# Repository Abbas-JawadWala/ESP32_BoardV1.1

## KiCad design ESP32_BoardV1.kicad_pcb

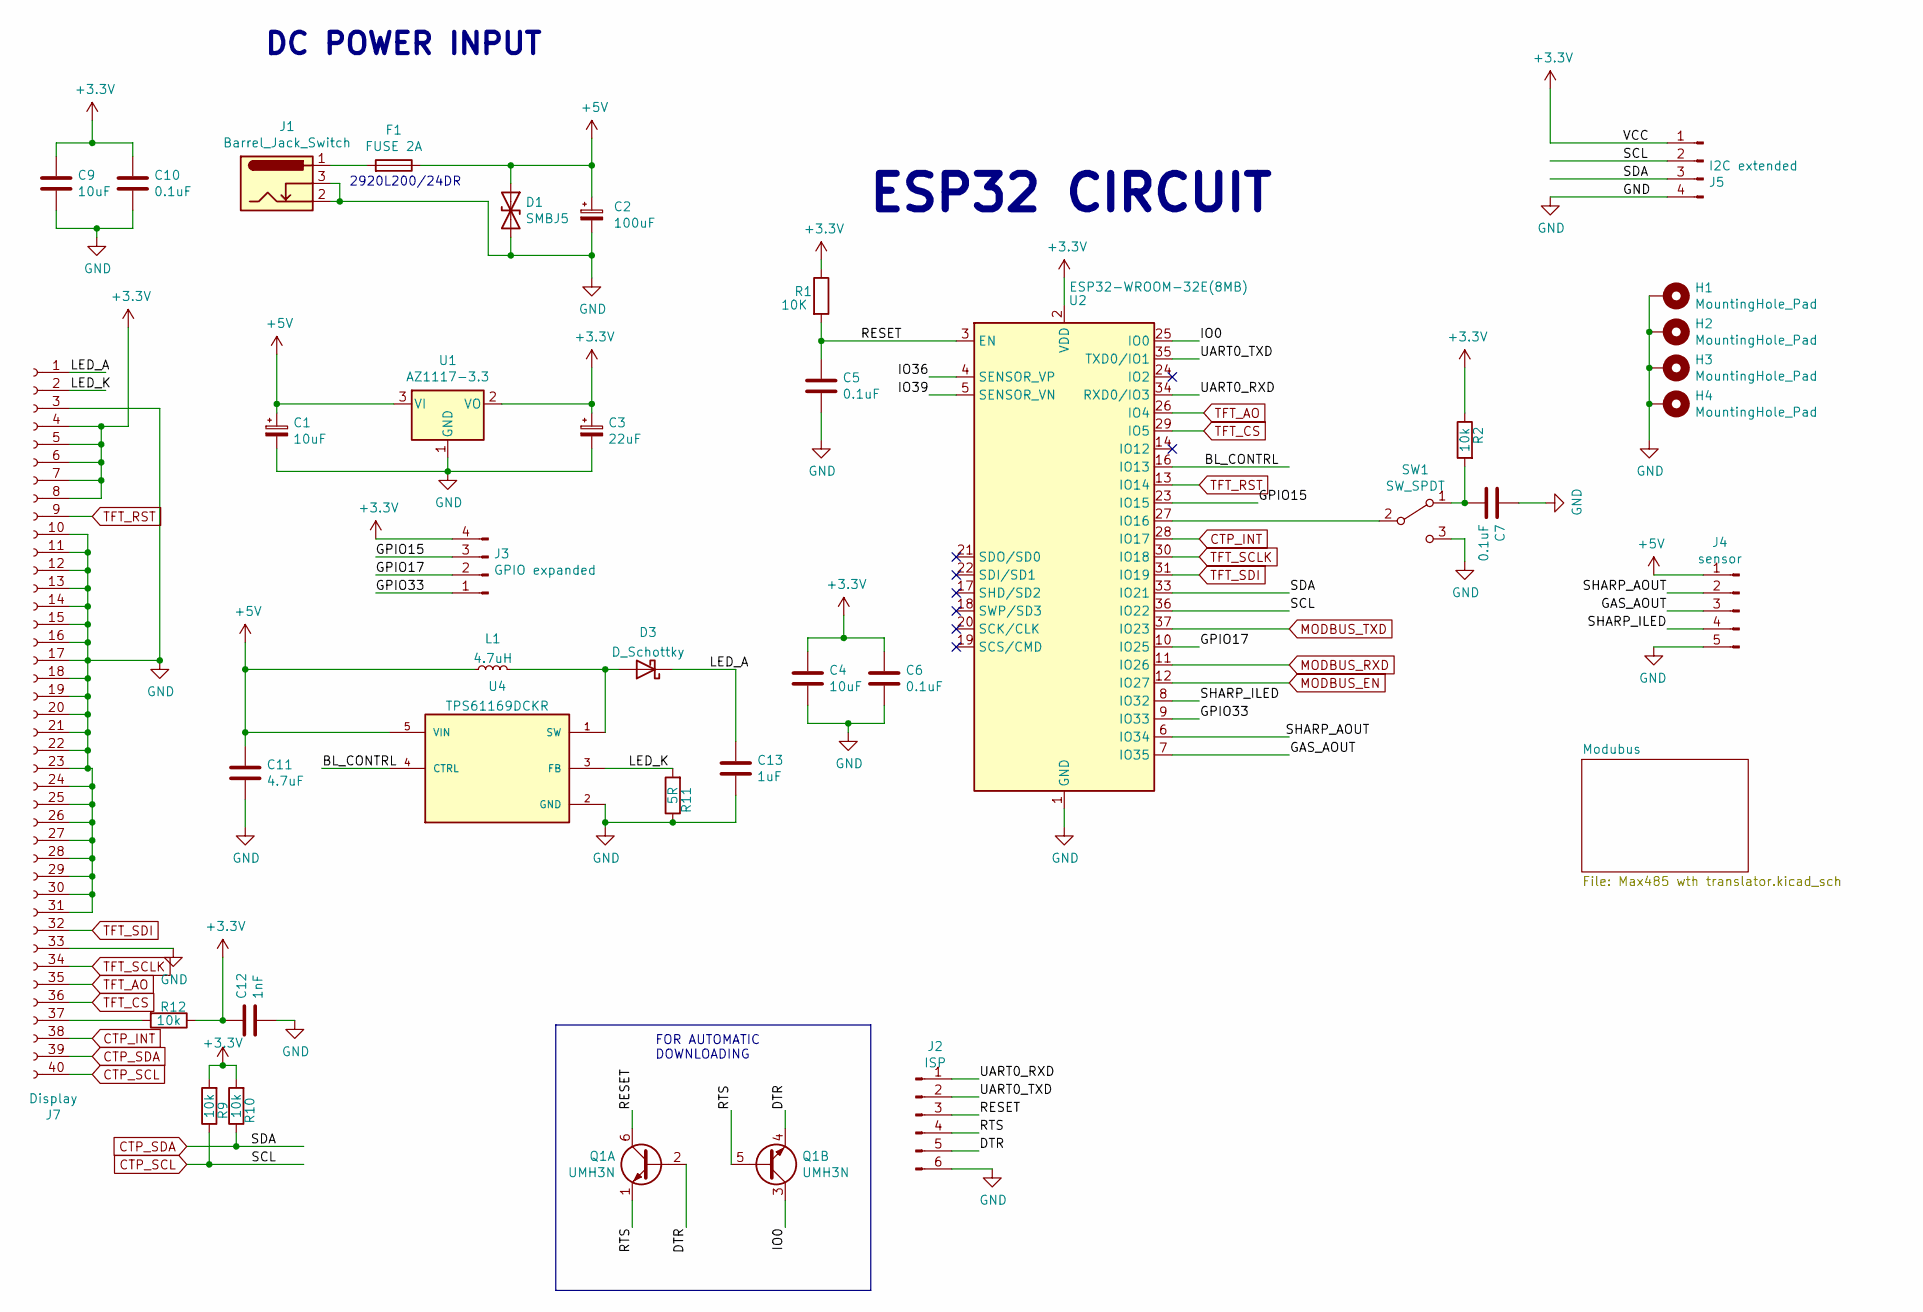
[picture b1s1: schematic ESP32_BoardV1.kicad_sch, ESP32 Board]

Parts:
C1: 10uF; CP_Elec_3x5.4
C2: 100uF; CP_Elec_6.3x5.4
C3: 22uF; CP_Elec_5x5.4
C4, C9: 10uF; C_0402_1005Metric_Pad0.74x0.62mm_HandSolder
C5, C6, C7, C10: 0.1uF; C_0402_1005Metric_Pad0.74x0.62mm_HandSolder
C11: 4.7uF; C_0402_1005Metric; MPN C1005X5R1A475K050BC
C12: 1nF; C_0402_1005Metric; MPN 0402ZC102KAT2A
C13: 1uF; C_0402_1005Metric; MPN C1005X6S1A105K050BC
D1: SMBJ5; D_SMB
D3: D_Schottky; D_SOD-123F; MPN RB160MM-90TR
F1: FUSE 2A; Fuse_1206_3216Metric
H1, H2, H3, H4: MountingHole_Pad; MountingHole_4.3mm_M4_Pad_Via
J1: Barrel_Jack_Switch; BarrelJack_CLIFF_FC681465S_SMT_Horizontal
J2: ISP; PinHeader_1x06_P2.54mm_Vertical
J3: GPIO expanded; JST_SM04B-SRSS-TB(LF)(SN); MPN JST_SM04B-SRSS-TB(LF)(SN)
J4: sensor; JST_SM05B-SRSS-TB(LF)(SN); MPN JST_SM05B-SRSS-TB(LF)(SN)
J5: I2C extended; JST_SM04B-SRSS-TB(LF)(SN); MPN JST_SM04B-SRSS-TB(LF)(SN)
J7: Display; Hirose_FH12-40S-0.5SH_1x40-1MP_P0.50mm_Horizontal
L1: 4.7uH; L_1008_2520Metric; MPN NRS4018T100MDGJ
Q1: UMH3N; SOT-363_SC-70-6
R1: 10K; R_0402_1005Metric_Pad0.72x0.64mm_HandSolder
R2, R9, R10, R12: 10k; R_0402_1005Metric_Pad0.72x0.64mm_HandSolder
R11: 5R; R_0402_1005Metric_Pad0.72x0.64mm_HandSolder
SW1: SW_SPDT; SW_Slide_1P2T_CK_OS102011MS2Q
U1: AZ1117-3.3; SOT-223-3_TabPin2; MPN AZ1117-3.3
U2: ESP32-WROOM-32E(8MB); ESP32-WROOM-32; MPN ESP32-WROOM-32
U4: TPS61169DCKR; SOT-353_SC-70-5; PARTREV A

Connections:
+3V3: C3.1, C4.1, C6.1, C9.1, C10.1, C12.1, J3.4, J5.1, J7.4, J7.5, J7.6, J7.7, J7.8, R1.1, R2.1, R9.2, R10.2, R12.1, U1.2 (VO), U2.2 (VDD); also elsewhere on the board
+5V: C1.1, C2.1, C11.1, D1.1 (A1), F1.1, J4.1, L1.1, U1.3 (VI), U4.5 (VIN)
/BL_CONTRL: U2.16 (IO13), U4.4 (CTRL)
/DTR: J2.5, Q1.2 (B1), Q1.4 (E2)
/GAS_AOUT: J4.3, U2.7 (IO35)
/GPIO15: J3.3, U2.23 (IO15)
/GPIO17: J3.2, U2.10 (IO25)
/GPIO33: J3.1, U2.9 (IO33)
/IO0: Q1.3 (C2), U2.25 (IO0)
/IO36: U2.4 (SENSOR_VP)
/IO39: U2.5 (SENSOR_VN)
/LED_A: C13.1, D3.1 (K), J7.1
/LED_K: J7.2, R11.2, U4.3 (FB)
/RESET: C5.1, J2.3, Q1.6 (C1), R1.2, U2.3 (EN)
/RTS: J2.4, Q1.1 (E1), Q1.5 (B2)
/SHARP_AOUT: J4.2, U2.6 (IO34)
/SHARP_ILED: J4.4, U2.8 (IO32)
/UART0_RXD: J2.1, U2.34 (RXD0/IO3)
/UART0_TXD: J2.2, U2.35 (TXD0/IO1)
CTP_INT: J7.38, U2.28 (IO17)
CTP_SCL: J5.2, J7.40, R9.1, U2.36 (IO22)
CTP_SDA: J5.3, J7.39, R10.1, U2.33 (IO21)
GND: C1.2, C2.2, C3.2, C4.2, C5.2, C6.2, C7.1, C9.2, C10.2, C11.2, C12.2, C13.2, D1.2 (A2), H1.1, H2.1, H3.1, H4.1, J1.2, J1.3, J2.6, J4.5, J5.4, J7.3, J7.10, J7.11, J7.12, J7.13, J7.14, J7.15, J7.16, J7.17, J7.18, J7.19, J7.20, J7.21, J7.22, J7.23, J7.24, J7.25, J7.26, J7.27, J7.28, J7.29, J7.30, J7.31, J7.33, R11.1, SW1.3 (C), U1.1 (GND), U2.1 (GND), U2.15 (GND), U2.38 (GND), U2.39 (GND), U4.2 (GND); also elsewhere on the board
MODBUS_EN: U2.12 (IO27); also elsewhere on the board
MODBUS_RXD: U2.11 (IO26); also elsewhere on the board
MODBUS_TXD: U2.37 (IO23); also elsewhere on the board
unnamed: C7.2, R2.2, SW1.1 (A)
unnamed: D3.2 (A), L1.2, U4.1 (SW)
unnamed: F1.2, J1.1
unnamed: J7.37, R12.2
unnamed: SW1.2 (B), U2.27 (IO16)
TFT_AO: J7.35, U2.26 (IO4)
TFT_CS: J7.36, U2.29 (IO5)
TFT_RST: J7.9, U2.13 (IO14)
TFT_SCLK: J7.34, U2.30 (IO18)
TFT_SDI: J7.32, U2.31 (IO19)

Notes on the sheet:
2920L200/24DR
FOR AUTOMATIC DOWNLOADING
DC POWER INPUT
ESP32 CIRCUIT

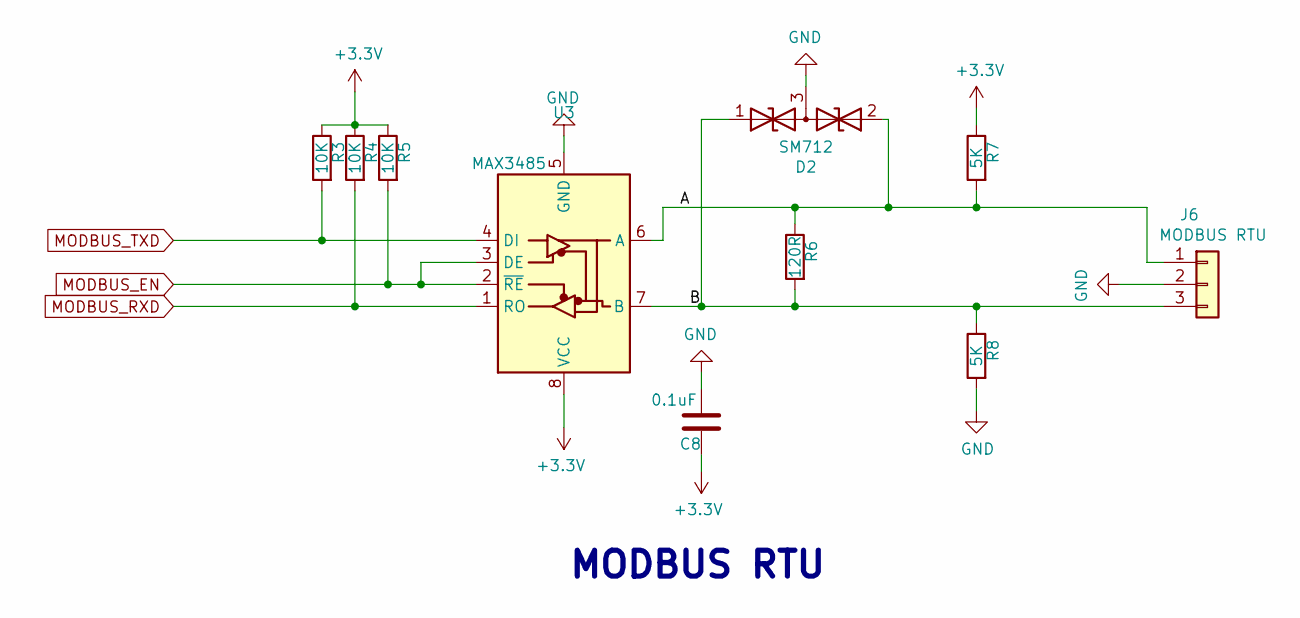
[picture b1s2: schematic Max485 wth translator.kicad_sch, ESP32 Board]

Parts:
C8: 0.1uF; C_0402_1005Metric_Pad0.74x0.62mm_HandSolder
D2: SM712; SOT-23
J6: MODBUS RTU; JST_SM03B-SRSS-TB(LF)(SN); MPN JST_SM03B-SRSS-TB(LF)(SN)
R3, R4, R5: 10K; R_0402_1005Metric_Pad0.72x0.64mm_HandSolder
R6: 120R; R_0402_1005Metric_Pad0.72x0.64mm_HandSolder
R7, R8: 5K; R_0402_1005Metric_Pad0.72x0.64mm_HandSolder
U3: MAX3485; SOIC-8_3.9x4.9mm_P1.27mm; MPN MAX3485

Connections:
+3V3: C8.2, R3.1, R4.1, R5.1, R7.1, U3.8 (VCC); also elsewhere on the board
/Modubus/A: D2.2 (A2), J6.1, R6.1, R7.2, U3.6 (A)
/Modubus/B: D2.1 (A1), J6.3, R6.2, R8.1, U3.7 (B)
GND: C8.1, D2.3 (common), J6.2, R8.2, U3.5 (GND); also elsewhere on the board
MODBUS_EN: R5.2, U3.2 (~RE), U3.3 (DE); also elsewhere on the board
MODBUS_RXD: R4.2, U3.1 (RO); also elsewhere on the board
MODBUS_TXD: R3.2, U3.4 (DI); also elsewhere on the board

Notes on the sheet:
MODBUS RTU

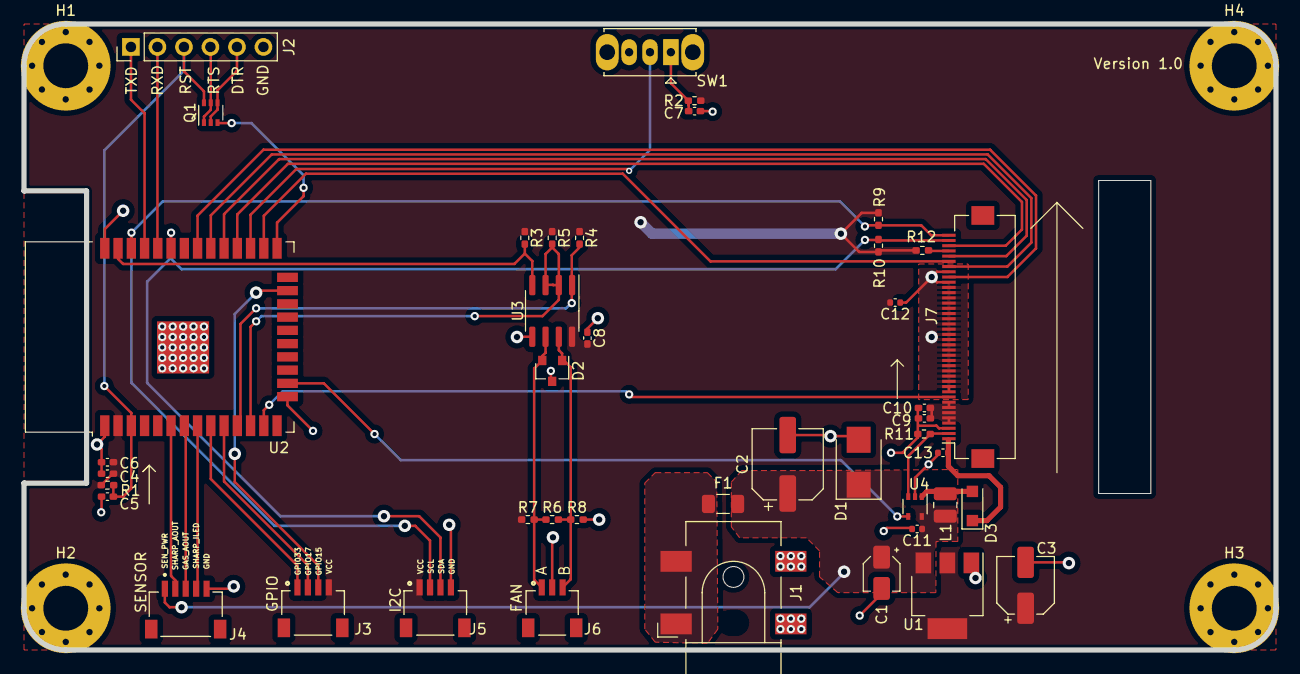
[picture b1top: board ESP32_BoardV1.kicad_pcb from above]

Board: 2 copper layers, 120.0 x 60.0 mm, 47 parts (0 on the bottom side), 36 nets.

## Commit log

2021-12-21 Recreated PCB file
    Removed old PCB files, Schematic error in existing PCB has been rectfied
2021-12-22 Pheripherial added 22.12.21
    Added display connector, I2C connector, button and MAX3485
2021-12-24 24.12.21
    Board layout added, Step file added
2021-12-27 PCB completed
2021-12-27 Schematics change
2021-12-27 pdf added
2021-12-28 Final draft
2021-12-31 Final draft with GERBER and Manufacturing Data
2022-01-01 Change 1/1/21
2022-01-01 added gebr and DFM data
2022-01-01 BOM CSV
2022-02-02 2/2/22
